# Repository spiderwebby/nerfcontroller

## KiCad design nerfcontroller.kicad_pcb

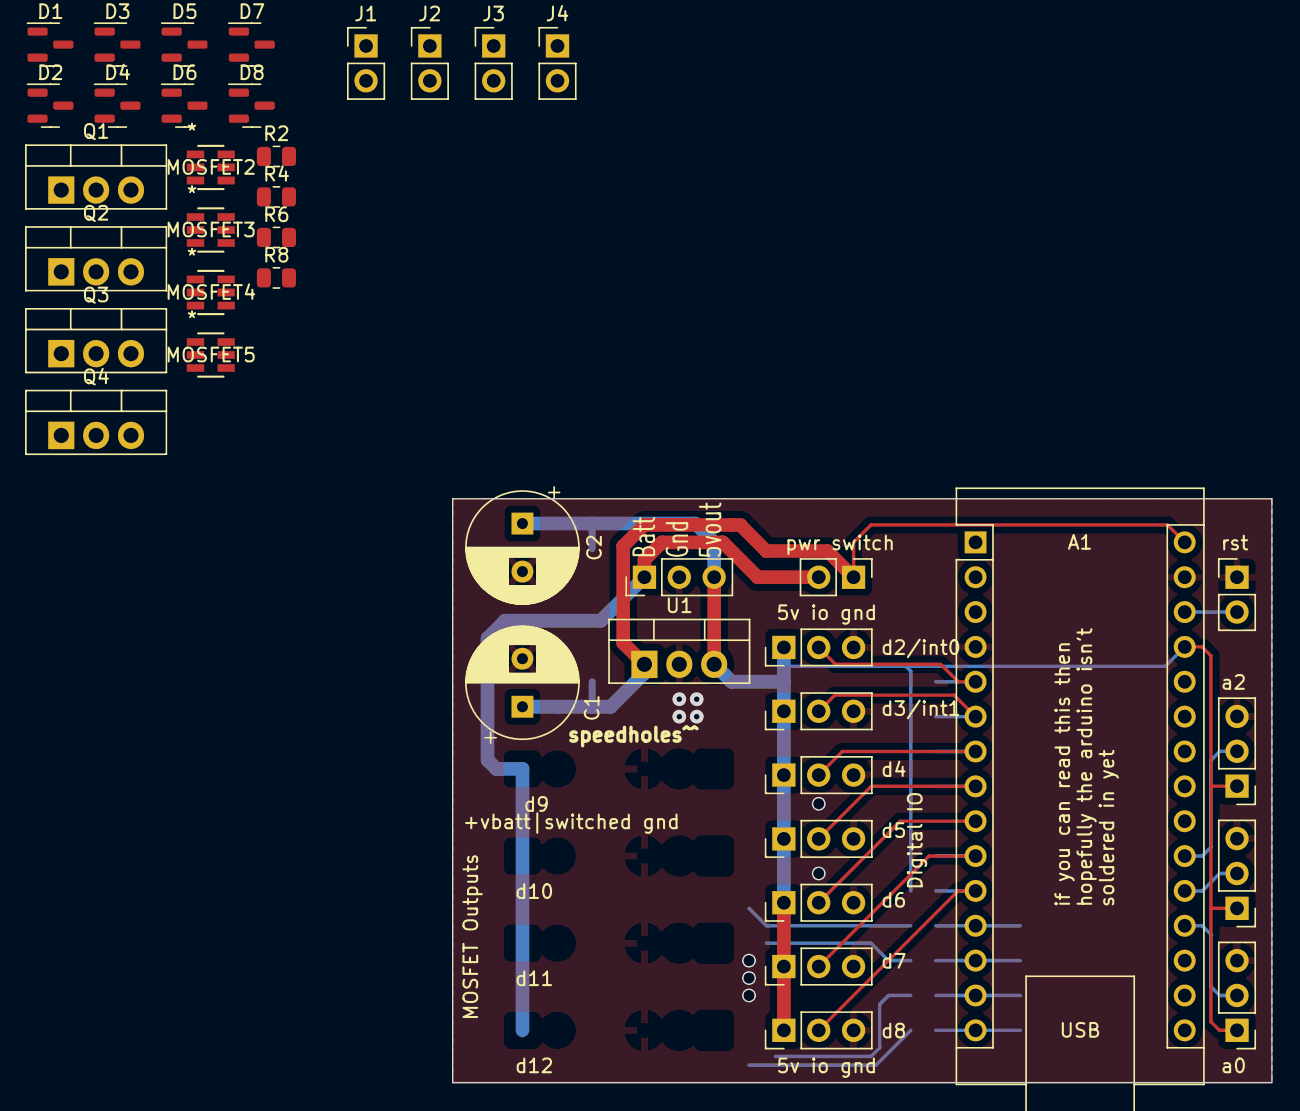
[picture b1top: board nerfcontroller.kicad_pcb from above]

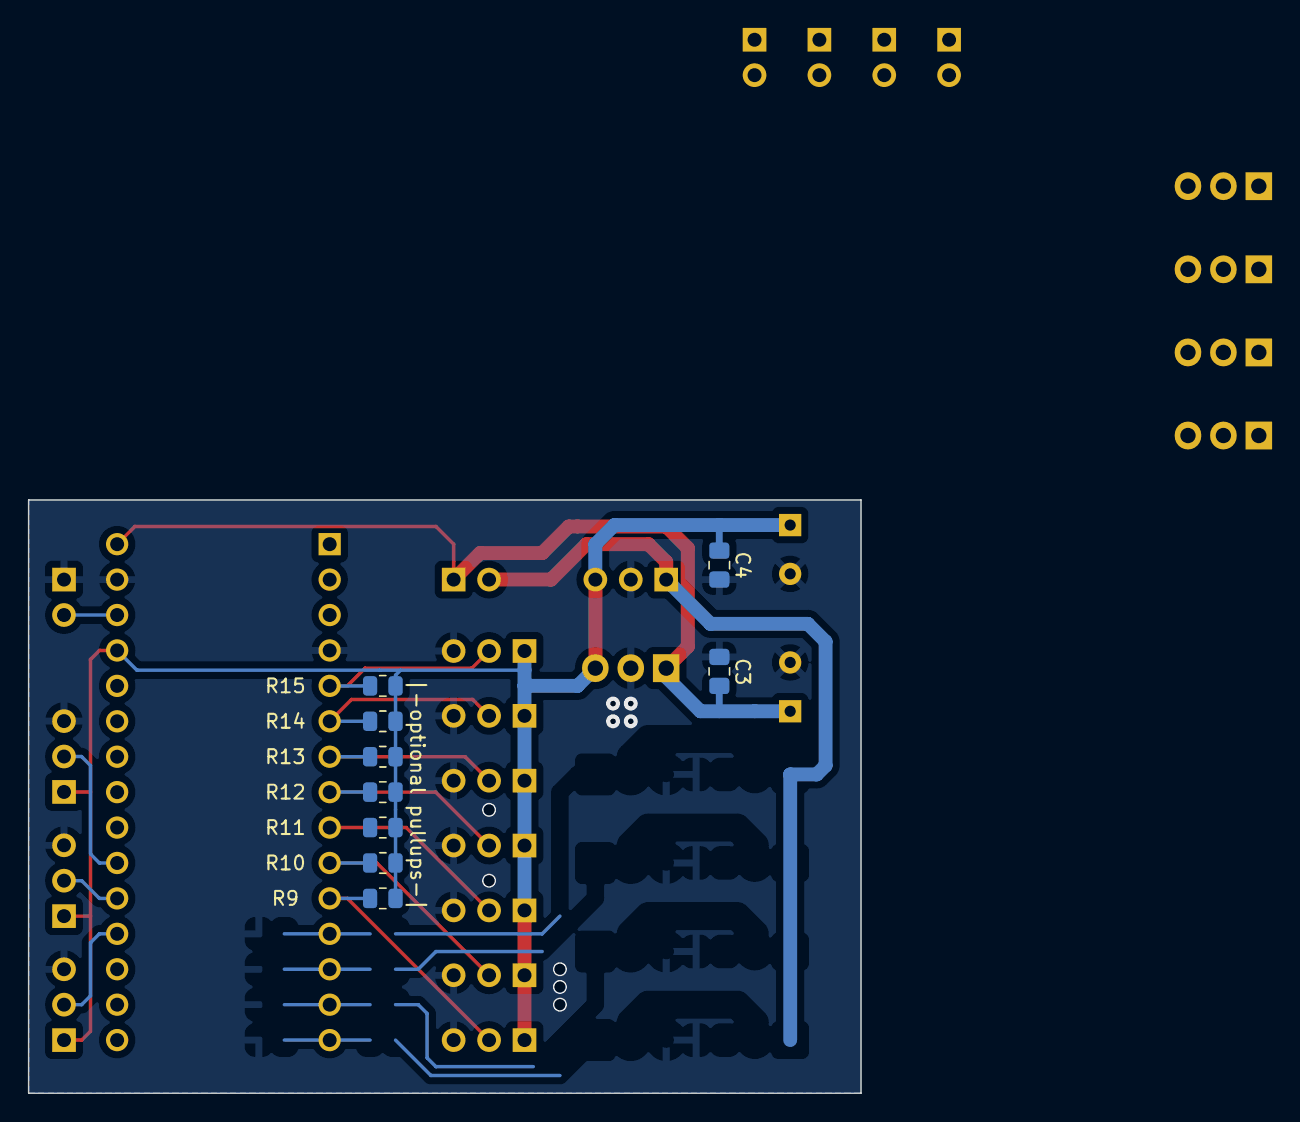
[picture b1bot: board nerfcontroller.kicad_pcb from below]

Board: 2 copper layers, 59.7 x 42.5 mm, 50 parts (9 on the bottom side), 35 nets.

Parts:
A1: Arduino_Nano_v3.x; Arduino_Nano
C1, C2: C; CP_Radial_D8.0mm_P3.50mm
C3, C4: C; C_0805_2012Metric_Pad1.18x1.45mm_HandSolder
D1, D2, D3, D4, D5, D6, D7, D8: BAV23C; SOT-23
J1, J2, J3, J4, J15, J16: Conn_01x02_Pin; PinHeader_1x02_P2.54mm_Vertical
J5, J6, J7, J8, J9, J10, J11, J12, J13, J14, J17: Conn_01x03_Pin; PinHeader_1x03_P2.54mm_Vertical
MOSFET2, MOSFET3, MOSFET4, MOSFET5: IRS10752LTRPBF; 6L-SOT23
Q1, Q2, Q3, Q4: IRL530; TO-220-3_Vertical
R2, R4, R6, R8: 4R7; R_0805_2012Metric
R9, R10, R11, R12, R13, R14, R15: R; R_0805_2012Metric
U1: LM7805_TO220; TO-220-3_Vertical

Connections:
+5V: A1.27 (+5V), C2.1, C4.1, D2.1 (A), D2.2 (A), D4.1 (A), D4.2 (A), D5.1 (A), D5.2 (A), D7.1 (A), D7.2 (A), J5.1, J6.1, J7.1, J8.1, J9.1, J10.1, J11.1, J12.1, J13.1, J14.1, J17.3, MOSFET2.1 (VCC), MOSFET3.1 (VCC), MOSFET4.1 (VCC), MOSFET5.1 (VCC), R9.1, R10.1, R11.1, R12.1, R13.1, R14.1, R15.1, U1.3 (VO)
+12V: J3.1, J4.1, J15.2, J17.1
/12v switched: A1.30 (VIN), C1.1, C3.1, J15.1, U1.1 (VI)
/a0: A1.19 (A0), J12.2
/a1: A1.20 (A1), J13.2
/a2: A1.21 (A2), J14.2
/d3: A1.6 (D3), J10.2, R14.2
/d4: A1.7 (D4), J9.2, R13.2
/d5: A1.8 (D5), J8.2, R12.2
/d6: A1.9 (D6), J7.2, R11.2
/d8: A1.11 (D8), J5.2, R9.2
/mosfet1: D1.3 (K), J4.2, Q4.2
/mosfet2: D3.3 (K), J3.2, Q1.2
/mosfet3: D6.3 (K), J2.2, Q2.2
/mosfet4: D8.3 (K), J1.2, Q3.2
/mosfets + drivers/D9 in: A1.12 (D9), MOSFET2.3 (IN)
/mosfets + drivers/D10 in: A1.13 (D10), MOSFET3.3 (IN)
/mosfets + drivers/D11 in: A1.14 (D11), MOSFET4.3 (IN)
/mosfets + drivers/D12 in: A1.15 (D12), MOSFET5.3 (IN)
/reset: A1.28 (~RESET), J16.2
GND: A1.4 (GND), A1.29 (GND), C1.2, C2.2, C3.2, C4.2, D1.1 (A), D1.2 (A), D3.1 (A), D3.2 (A), D6.1 (A), D6.2 (A), D8.1 (A), D8.2 (A), J1.1, J2.1, J5.3, J6.3, J7.3, J8.3, J9.3, J10.3, J11.3, J12.3, J13.3, J14.3, J16.1, J17.2, MOSFET2.2 (COM), MOSFET2.4 (VS), MOSFET3.2 (COM), MOSFET3.4 (VS), MOSFET4.2 (COM), MOSFET4.4 (VS), MOSFET5.2 (COM), MOSFET5.4 (VS), Q1.3, Q2.3, Q3.3, Q4.3, U1.2 (GND)
unnamed: A1.5 (D2), J11.2, R15.2
unnamed: A1.10 (D7), J6.2, R10.2
unnamed: D2.3 (K), MOSFET3.6 (VB)
unnamed: D4.3 (K), MOSFET4.6 (VB)
unnamed: D5.3 (K), MOSFET2.6 (VB)
unnamed: D7.3 (K), MOSFET5.6 (VB)
unnamed: MOSFET2.5 (HO), R8.2
unnamed: MOSFET3.5 (HO), R2.2
unnamed: MOSFET4.5 (HO), R4.2
unnamed: MOSFET5.5 (HO), R6.2
unnamed: Q1.1, R2.1
unnamed: Q2.1, R4.1
unnamed: Q3.1, R6.1
unnamed: Q4.1, R8.1

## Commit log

2023-11-29 update ignored files
2023-12-23 added resistor values for mosfets
2023-12-23 gerbers folder added to gitignore
2023-12-23 initial + set up basic IO
2023-12-24 added calcs for FPS + projectile energy
2023-12-25 basic functionality implemented
2023-12-25 added serialprint spam for testing
2023-12-25 added triger sequencing, fixed overlapping solenoid set/reset issue, tested and working in teleplot.
2023-12-29 corrected resistor values + silkscreen goofs
2023-12-29 added hall effect trigger
2023-12-29 added the albatros quadbarrel
2023-12-29 made it work for test
2023-12-29 fixed pin naming goof
2024-01-05 added mosfet drivers and sot23 diodes
2024-01-05 mosfet driver sheet
